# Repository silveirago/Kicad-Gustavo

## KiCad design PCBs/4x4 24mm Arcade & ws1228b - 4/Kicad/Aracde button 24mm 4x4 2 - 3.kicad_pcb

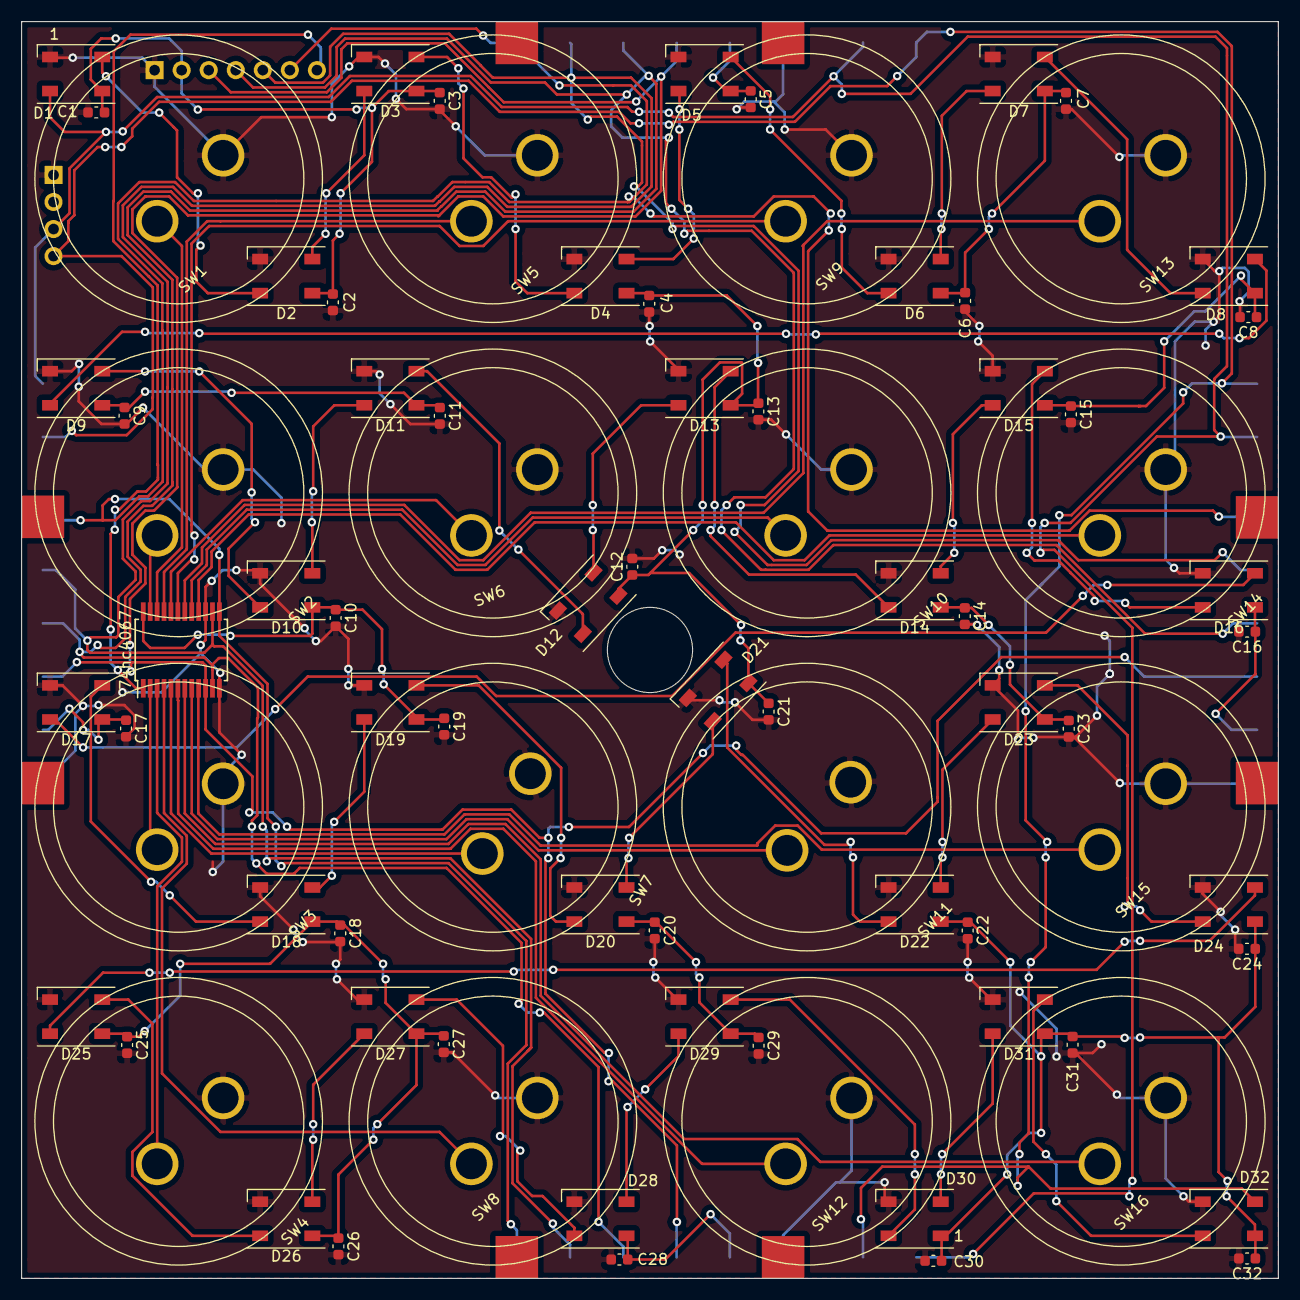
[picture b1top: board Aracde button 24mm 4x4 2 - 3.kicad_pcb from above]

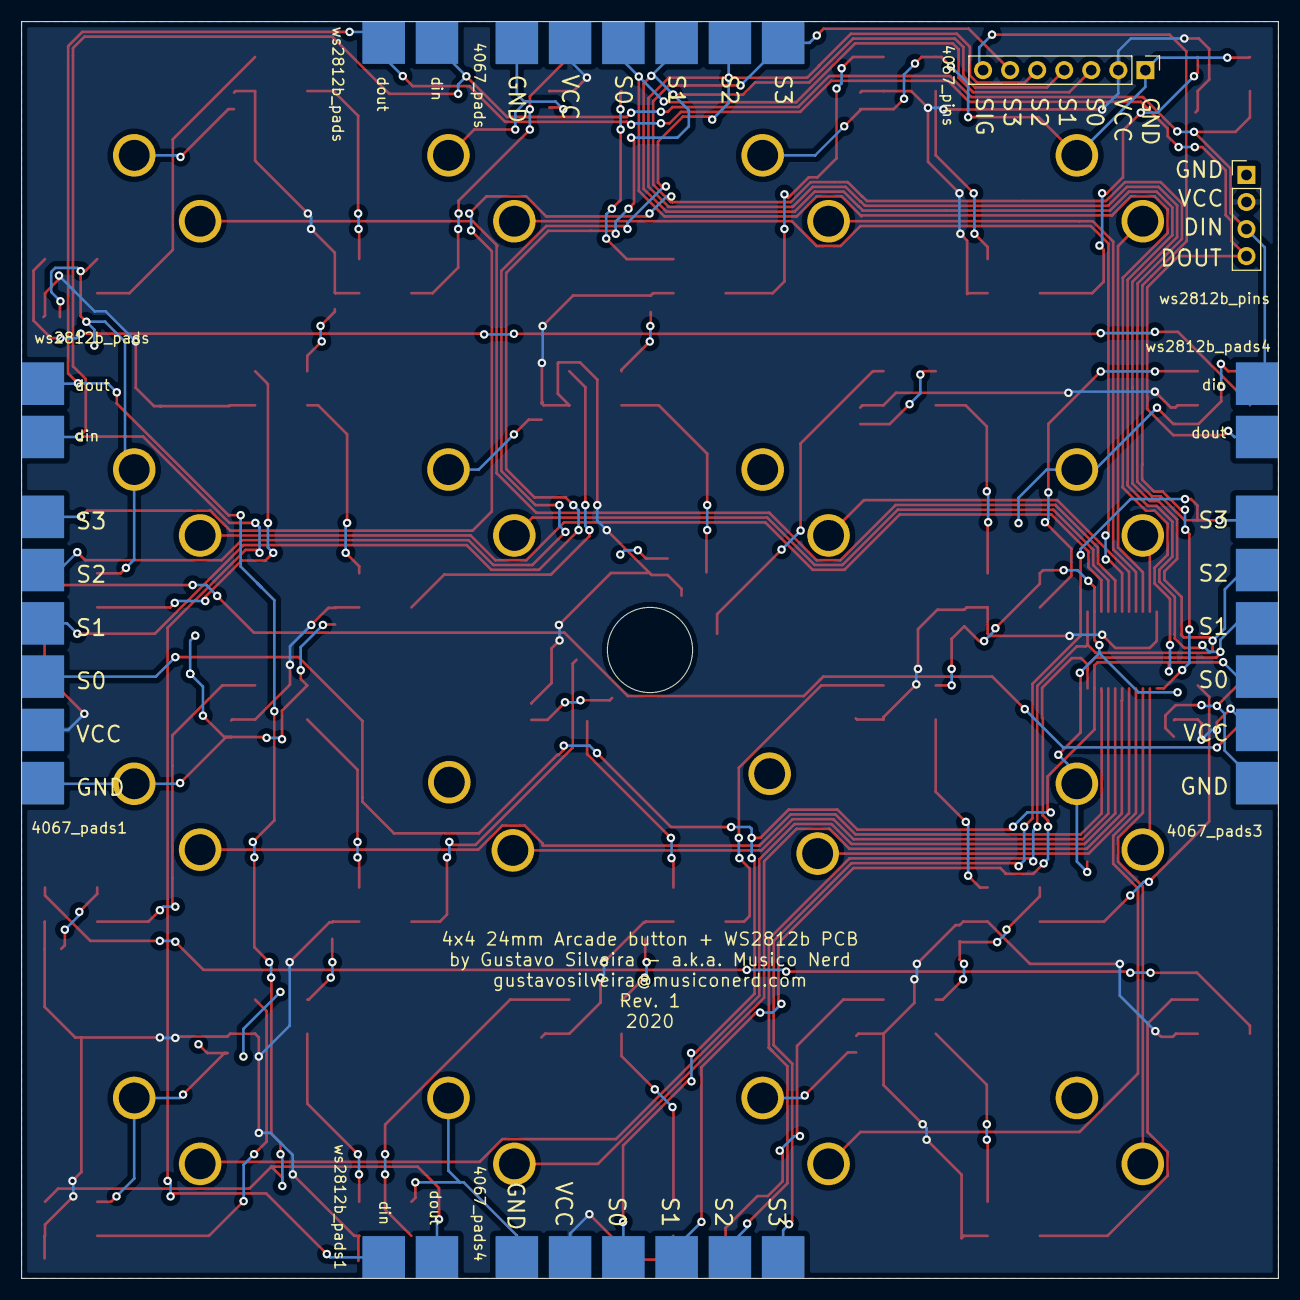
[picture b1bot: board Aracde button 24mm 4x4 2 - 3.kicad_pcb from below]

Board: 2 copper layers, 118.0 x 118.0 mm, 91 parts (10 on the bottom side), 56 nets.

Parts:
74hc4067: CD74HC4067M; SSOP-24_5.3x8.2mm_P0.65mm
4067_pads, 4067_pads1, 4067_pads3, 4067_pads4: Conn_01x06_Female; pad_connector_small_6
4067_pins: Conn_01x07_Female; PinHeader_1x07_P2.54mm_Vertical
C1, C2, C3, C4, C5, C6, C7, C8, C9, C10, C11, C12, C13, C14, C15, C16, C17, C18, C19, C20, C21, C22, C23, C24, C25, C26, C27, C28, C29, C30, C31, C32: 100nF; C_0603_1608Metric
D1, D2, D3, D4, D5, D6, D7, D8, D9, D10, D11, D12, D13, D14, D15, D16, D17, D18, D19, D20, D21, D22, D23, D24, D25, D26, D27, D28, D29, D30, D31, D32: WS2812B; LED_WS2812B_PLCC4_5.0x5.0mm_P3.2mm
SW1, SW2, SW3, SW4, SW5, SW6, SW7, SW8, SW9, SW10, SW11, SW12, SW13, SW14, SW15, SW16: SW_SPST; Arcade button 24mm
ws2812b_pads, ws2812b_pads1, ws2812b_pads4, ws2812b_pads#2: Conn_01x02_Female; pad_connector_small_2
ws2812b_pins: Conn_01x04_Female; PinHeader_1x04_P2.54mm_Vertical

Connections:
/S0: 74hc4067.10, 4067_pads.3, 4067_pads1.3, 4067_pads3.3, 4067_pads4.3, 4067_pins.3
/S1: 74hc4067.11, 4067_pads.4, 4067_pads1.4, 4067_pads3.4, 4067_pads4.4, 4067_pins.4
/S2: 74hc4067.14, 4067_pads.5, 4067_pads1.5, 4067_pads3.5, 4067_pads4.5, 4067_pins.5
/S3: 74hc4067.13, 4067_pads.6, 4067_pads1.6, 4067_pads3.6, 4067_pads4.6, 4067_pins.6
/SIG: 74hc4067.1, 4067_pins.7
/din: D1.4, ws2812b_pads.1, ws2812b_pads1.1, ws2812b_pads4.2, ws2812b_pads#2.2, ws2812b_pins.3
/dout: D32.2, ws2812b_pads.2, ws2812b_pads1.2, ws2812b_pads4.1, ws2812b_pads#2.1, ws2812b_pins.4
/mux_0: 74hc4067.9, SW15.1
/mux_1: 74hc4067.8, SW11.1
/mux_2: 74hc4067.7, SW16.1
/mux_3: 74hc4067.6, SW12.1
/mux_4: 74hc4067.5, SW7.1
/mux_5: 74hc4067.4, SW8.1
/mux_6: 74hc4067.3, SW4.1
/mux_7: 74hc4067.2, SW3.1
/mux_8: 74hc4067.23, SW2.1
/mux_9: 74hc4067.22, SW1.1
/mux_10: 74hc4067.21, SW5.1
/mux_11: 74hc4067.20, SW6.1
/mux_12: 74hc4067.19, SW9.1
/mux_13: 74hc4067.18, SW13.1
/mux_14: 74hc4067.17, SW10.1
/mux_15: 74hc4067.16, SW14.1
GND: 74hc4067.12, 74hc4067.15, 4067_pads.1, 4067_pads1.1, 4067_pads3.1, 4067_pads4.1, 4067_pins.1, C1.2, C2.2, C3.2, C4.2, C5.2, C6.2, C7.2, C8.2, C9.2, C10.2, C11.2, C12.2, C13.2, C14.2, C15.2, C16.2, C17.2, C18.2, C19.2, C20.2, C21.2, C22.2, C23.2, C24.2, C25.2, C26.2, C27.2, C28.2, C29.2, C30.2, C31.2, C32.2, D1.3, D2.3, D3.3, D4.3, D5.3, D6.3, D7.3, D8.3, D9.3, D10.3, D11.3, D12.3, D13.3, D14.3, D15.3, D16.3, D17.3, D18.3, D19.3, D20.3, D21.3, D22.3, D23.3, D24.3, D25.3, D26.3, D27.3, D28.3, D29.3, D30.3, D31.3, D32.3, SW1.2, SW2.2, SW3.2, SW4.2, SW5.2, SW6.2, SW7.2, SW8.2, SW9.2, SW10.2, SW11.2, SW12.2, SW13.2, SW14.2, SW15.2, SW16.2, ws2812b_pins.1
unnamed: D1.2, D2.4
unnamed: D2.2, D3.4
unnamed: D3.2, D4.4
unnamed: D4.2, D5.4
unnamed: D5.2, D6.4
unnamed: D6.2, D7.4
unnamed: D7.2, D8.4
unnamed: D8.2, D9.4
unnamed: D10.2, D11.4
unnamed: D9.2, D10.4
unnamed: D11.2, D12.4
unnamed: D12.2, D13.4
unnamed: D13.2, D14.4
unnamed: D14.2, D15.4
unnamed: D15.2, D16.4
unnamed: D16.2, D17.4
unnamed: D17.2, D18.4
unnamed: D18.2, D19.4
unnamed: D19.2, D20.4
unnamed: D20.2, D21.4
unnamed: D21.2, D22.4
unnamed: D22.2, D23.4
unnamed: D23.2, D24.4
unnamed: D24.2, D25.4
unnamed: D25.2, D26.4
unnamed: D26.2, D27.4
unnamed: D27.2, D28.4
unnamed: D28.2, D29.4
unnamed: D29.2, D30.4
unnamed: D30.2, D31.4
unnamed: D31.2, D32.4
VCC: 74hc4067.24, 4067_pads.2, 4067_pads1.2, 4067_pads3.2, 4067_pads4.2, 4067_pins.2, C1.1, C2.1, C3.1, C4.1, C5.1, C6.1, C7.1, C8.1, C9.1, C10.1, C11.1, C12.1, C13.1, C14.1, C15.1, C16.1, C17.1, C18.1, C19.1, C20.1, C21.1, C22.1, C23.1, C24.1, C25.1, C26.1, C27.1, C28.1, C29.1, C30.1, C31.1, C32.1, D1.1, D2.1, D3.1, D4.1, D5.1, D6.1, D7.1, D8.1, D9.1, D10.1, D11.1, D12.1, D13.1, D14.1, D15.1, D16.1, D17.1, D18.1, D19.1, D20.1, D21.1, D22.1, D23.1, D24.1, D25.1, D26.1, D27.1, D28.1, D29.1, D30.1, D31.1, D32.1, ws2812b_pins.2

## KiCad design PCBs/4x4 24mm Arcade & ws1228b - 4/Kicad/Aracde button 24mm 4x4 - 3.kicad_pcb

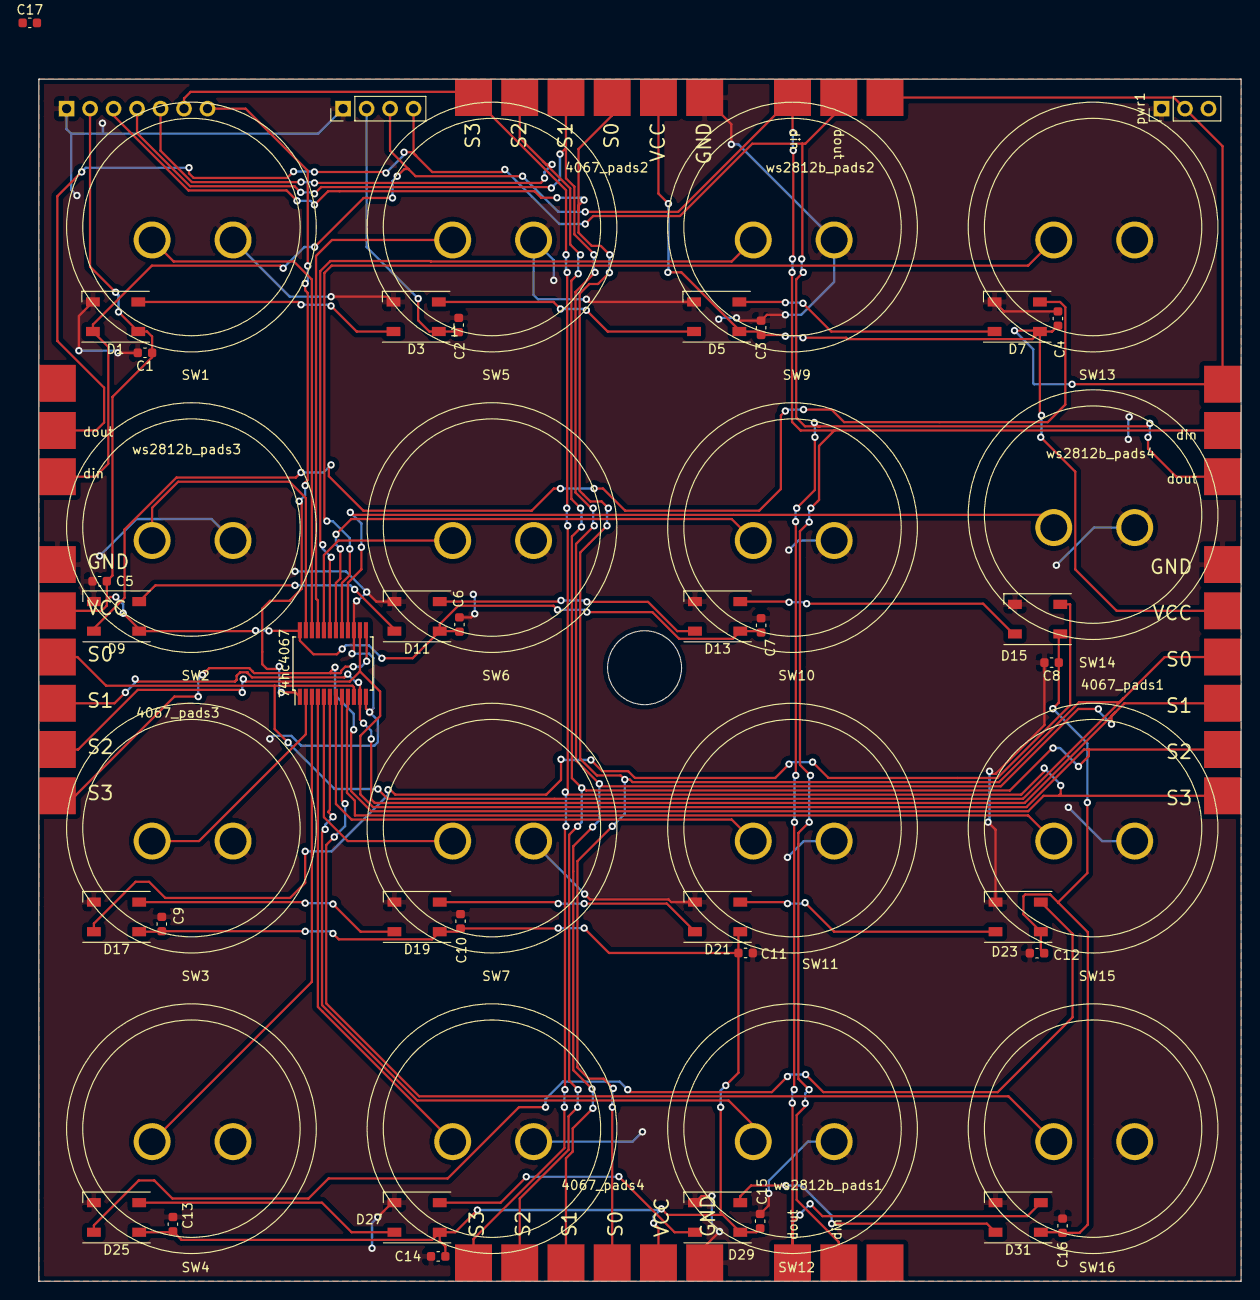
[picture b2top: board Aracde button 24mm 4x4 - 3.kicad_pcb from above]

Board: 2 copper layers, 130.0 x 130.0 mm, 65 parts (1 on the bottom side), 41 nets.

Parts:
5v1, 5v2, 5v3, 5v4: pad_5v; Pad_connector_small
74hc4067: CD74HC4067M; SSOP-24_5.3x8.2mm_P0.65mm
4067_pads1, 4067_pads2, 4067_pads3, 4067_pads4: Conn_01x06_Female; pad_connector_small_6
4067_pins1: Conn_01x07_Female; PinHeader_1x07_P2.54mm_Vertical
C1, C2, C3, C4, C5, C6, C7, C8, C9, C10, C11, C12, C13, C14, C15, C16, C17: 100nF; C_0603_1608Metric
D1, D3, D5, D7, D9, D11, D13, D15, D17, D19, D21, D23, D25, D27, D29, D31: WS2812B; LED_WS2812B_PLCC4_5.0x5.0mm_P3.2mm
SW1, SW2, SW3, SW4, SW5, SW6, SW7, SW8, SW9, SW10, SW11, SW12, SW13, SW14, SW15, SW16: SW_SPST; Arcade button 24mm
pwr1: Conn_01x03_Female; PinHeader_1x03_P2.54mm_Vertical
ws2812b_pads1, ws2812b_pads2, ws2812b_pads3, ws2812b_pads4: Conn_01x02_Female; pad_connector_small_2
ws2812b_pins4: Conn_01x04_Female; PinHeader_1x04_P2.54mm_Vertical

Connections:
+5V: 5v1.1, 5v2.1, 5v3.1, 5v4.1, C1.1, C2.1, C3.1, C4.1, C5.1, C6.1, C7.1, C8.1, C9.1, C10.1, C11.1, C12.1, C13.1, C14.1, C15.1, C16.1, D1.1, D3.1, D5.1, D7.1, D9.1, D11.1, D13.1, D15.1, D17.1, D19.1, D21.1, D23.1, D25.1, D27.1, D29.1, D31.1, pwr1.2, ws2812b_pins4.2
/S0: 74hc4067.10, 4067_pads1.3, 4067_pads2.3, 4067_pads3.3, 4067_pads4.3, 4067_pins1.3
/S1: 74hc4067.11, 4067_pads1.4, 4067_pads2.4, 4067_pads3.4, 4067_pads4.4, 4067_pins1.4
/S2: 74hc4067.14, 4067_pads1.5, 4067_pads2.5, 4067_pads3.5, 4067_pads4.5, 4067_pins1.5
/S3: 74hc4067.13, 4067_pads1.6, 4067_pads2.6, 4067_pads3.6, 4067_pads4.6, 4067_pins1.6
/SIG: 74hc4067.1, 4067_pins1.7
/din: D1.4, ws2812b_pads1.1, ws2812b_pads2.2, ws2812b_pads3.1, ws2812b_pads4.2, ws2812b_pins4.3
/dout: D31.2, ws2812b_pads1.2, ws2812b_pads2.1, ws2812b_pads3.2, ws2812b_pads4.1, ws2812b_pins4.4
/mux_0: 74hc4067.9, SW15.1
/mux_1: 74hc4067.8, SW16.1
/mux_2: 74hc4067.7, SW11.1
/mux_3: 74hc4067.6, SW12.1
/mux_4: 74hc4067.5, SW7.1
/mux_5: 74hc4067.4, SW8.1
/mux_6: 74hc4067.3, SW4.1
/mux_7: 74hc4067.2, SW3.1
/mux_8: 74hc4067.23, SW2.1
/mux_9: 74hc4067.22, SW1.1
/mux_10: 74hc4067.21, SW5.1
/mux_11: 74hc4067.20, SW6.1
/mux_12: 74hc4067.19, SW9.1
/mux_13: 74hc4067.18, SW10.1
/mux_14: 74hc4067.17, SW13.1
/mux_15: 74hc4067.16, SW14.1
GND: 74hc4067.12, 74hc4067.15, 4067_pads1.1, 4067_pads2.1, 4067_pads3.1, 4067_pads4.1, 4067_pins1.1, C1.2, C2.2, C3.2, C4.2, C5.2, C6.2, C7.2, C8.2, C9.2, C10.2, C11.2, C12.2, C13.2, C14.2, C15.2, C16.2, C17.1, D1.3, D3.3, D5.3, D7.3, D9.3, D11.3, D13.3, D15.3, D17.3, D19.3, D21.3, D23.3, D25.3, D27.3, D29.3, D31.3, SW1.2, SW2.2, SW3.2, SW4.2, SW5.2, SW6.2, SW7.2, SW8.2, SW9.2, SW10.2, SW11.2, SW12.2, SW13.2, SW14.2, SW15.2, SW16.2, pwr1.1, ws2812b_pins4.1
unnamed: D1.2, D3.4
unnamed: D3.2, D5.4
unnamed: D5.2, D7.4
unnamed: D7.2, D9.4
unnamed: D11.2, D13.4
unnamed: D9.2, D11.4
unnamed: D13.2, D15.4
unnamed: D15.2, D17.4
unnamed: D17.2, D19.4
unnamed: D19.2, D21.4
unnamed: D21.2, D23.4
unnamed: D23.2, D25.4
unnamed: D25.2, D27.4
unnamed: D27.2, D29.4
unnamed: D29.2, D31.4
VCC: 74hc4067.24, 4067_pads1.2, 4067_pads2.2, 4067_pads3.2, 4067_pads4.2, 4067_pins1.2, C17.2, pwr1.3

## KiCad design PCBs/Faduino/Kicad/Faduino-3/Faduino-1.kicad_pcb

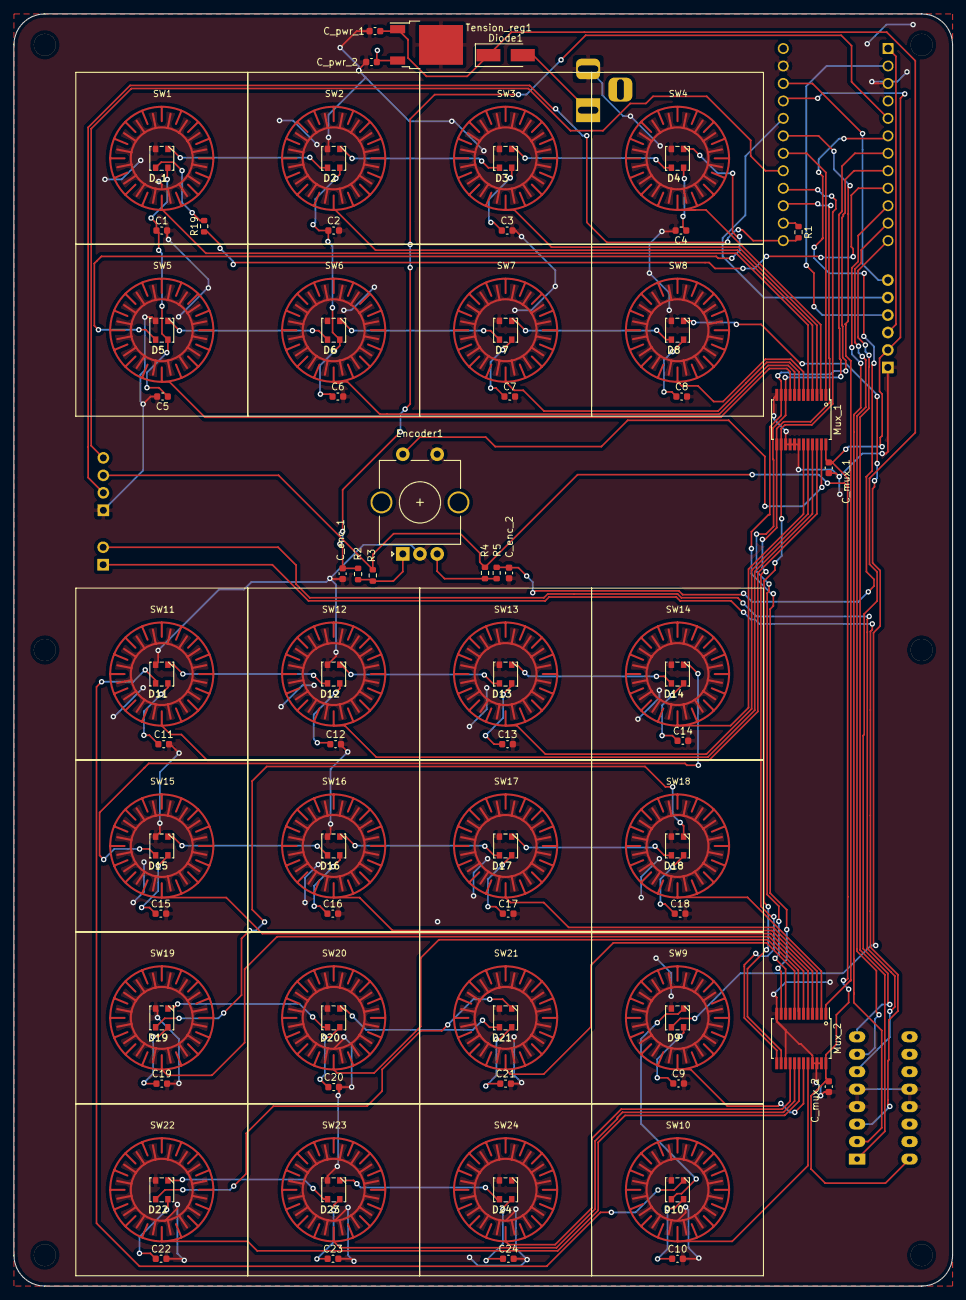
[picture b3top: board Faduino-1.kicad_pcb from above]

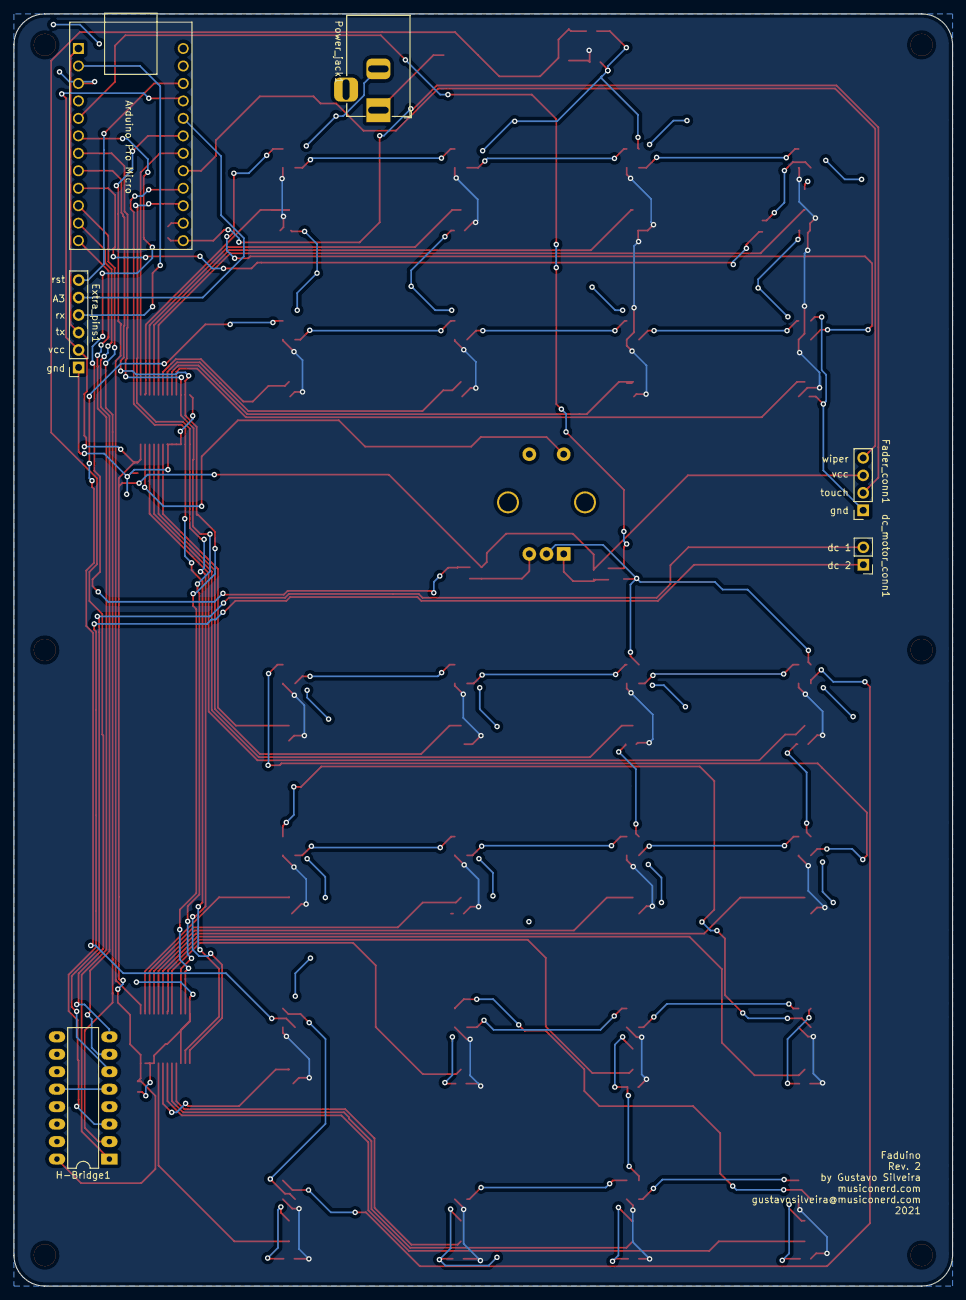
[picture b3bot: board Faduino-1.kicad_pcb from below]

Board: 2 copper layers, 136.5 x 185.0 mm, 95 parts (6 on the bottom side), 77 nets.

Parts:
Arduino Pro Micro: Arduino_Pro_Micro; ArduinoProMicro
C1, C2, C3, C4, C5, C6, C7, C8, C9, C10, C11, C12, C13, C14, C15, C16, C17, C18, C19, C20, C21, C22, C23, C24: 100nF; C_0603_1608Metric
C_enc_1, C_enc_2: 10nF; C_0603_1608Metric
C_mux_1, C_mux_2: 100nF; C_0603_1608Metric
C_pwr_1: 330nF; C_0603_1608Metric
C_pwr_2: 100nF; C_0603_1608Metric
D2, D3, D4, D5, D6, D7, D8, D9, D10, D11, D12, D13, D14, D15, D16, D17, D18, D19, D20, D21, D22, D23, D24: WS2812B; WS2812B-mini-V3
D_1: WS2812B; WS2812B-mini-V3
Diode1: 1N4007; D_SMA_Handsoldering
Encoder1: Rotary_Encoder_Switch; RotaryEncoder_Alps_EC11E-Switch_Vertical_H20mm_CircularMoun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
Extra_pins1: Conn_01x06; PinSocket_1x06_P2.54mm_Vertical
Fader_conn1: Conn_01x04; PinSocket_1x04_P2.54mm_Vertical
H-Bridge1: L293D; DIP-16_W7.62mm_LongPads
Mux_1, Mux_2: CD74HC4067M_2; SSOP-24_5.3x8.2mm_P0.65mm
Power_jack1: Jack-DC; BarrelJack_Horizontal
R1: 1M; R_0603_1608Metric
R2, R3, R4, R5: 10k; R_0603_1608Metric
R19: 330; R_0603_1608Metric
SW1, SW2, SW3, SW4, SW5, SW6, SW7, SW8, SW9, SW10, SW11, SW12, SW13, SW14, SW15, SW16, SW17, SW18, SW19, SW20, SW21, SW22, SW23, SW24: SW_SPST; rubber_pad_sw_5
Tension_reg1: L7805; TO-252-2
dc_motor_conn1: Conn_01x02; PinHeader_1x02_P2.54mm_Vertical

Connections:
5V: C1.1, C2.1, C3.1, C4.1, C5.1, C6.1, C7.1, C8.1, C9.1, C10.1, C11.1, C12.1, C13.1, C14.1, C15.1, C16.1, C17.1, C18.1, C19.1, C20.1, C21.1, C22.1, C23.1, C24.1, C_pwr_2.1, D2.1, D3.1, D4.1, D5.1, D6.1, D7.1, D8.1, D9.1, D10.1, D11.1, D12.1, D13.1, D14.1, D15.1, D16.1, D17.1, D18.1, D19.1, D20.1, D21.1, D22.1, D23.1, D24.1, D_1.1, Tension_reg1.3
9V: C_pwr_1.1, Diode1.1, H-Bridge1.8, Tension_reg1.1
/A3: Arduino Pro Micro.20, Extra_pins1.5
/RST: Arduino Pro Micro.22, Extra_pins1.6
/RX: Arduino Pro Micro.2, Extra_pins1.4
/TX: Arduino Pro Micro.1, Extra_pins1.3
ENC_A: Arduino Pro Micro.5, C_enc_1.1, R2.2
ENC_B: Arduino Pro Micro.6, C_enc_2.1, R5.1
ENC_SW: Encoder1.S2, Mux_1.23
F_ENABLE: Arduino Pro Micro.12, H-Bridge1.1
F_IN_1: Arduino Pro Micro.10, H-Bridge1.2
F_IN_2: Arduino Pro Micro.11, H-Bridge1.7
F_OUT_1: H-Bridge1.3, dc_motor_conn1.1
F_OUT_2: H-Bridge1.6, dc_motor_conn1.2
F_TOUCH_1: Arduino Pro Micro.13, Fader_conn1.2, R1.2
F_TOUCH_2: Arduino Pro Micro.14, R1.1
F_WIPER: Arduino Pro Micro.17, Fader_conn1.4
GND: Arduino Pro Micro.3, Arduino Pro Micro.4, Arduino Pro Micro.23, C1.2, C2.2, C3.2, C4.2, C5.2, C6.2, C7.2, C8.2, C9.2, C10.2, C11.2, C12.2, C13.2, C14.2, C15.2, C16.2, C17.2, C18.2, C19.2, C20.2, C21.2, C22.2, C23.2, C24.2, C_enc_1.2, C_enc_2.2, C_mux_1.2, C_mux_2.2, C_pwr_1.2, C_pwr_2.2, D2.3, D3.3, D4.3, D5.3, D6.3, D7.3, D8.3, D9.3, D10.3, D11.3, D12.3, D13.3, D14.3, D15.3, D16.3, D17.3, D18.3, D19.3, D20.3, D21.3, D22.3, D23.3, D24.3, D_1.3, Encoder1.C, Encoder1.S1, Extra_pins1.1, Fader_conn1.1, H-Bridge1.4, H-Bridge1.5, H-Bridge1.12, H-Bridge1.13, Mux_1.12, Mux_1.15, Mux_1.16, Mux_1.17, Mux_1.18, Mux_2.12, Mux_2.15, Mux_2.21, Mux_2.22, Mux_2.23, Power_jack1.2, SW1.1, SW2.1, SW3.1, SW4.1, SW5.1, SW6.1, SW7.1, SW8.1, SW9.1, SW10.1, SW11.1, SW12.1, SW13.1, SW14.1, SW15.1, SW16.1, SW17.1, SW18.1, SW19.1, SW20.1, SW21.1, SW22.1, SW23.1, SW24.1, Tension_reg1.2
unnamed: D2.2, D3.4
unnamed: D2.4, D_1.2
unnamed: D3.2, D4.4
unnamed: D4.2, D5.4
unnamed: D5.2, D6.4
unnamed: D6.2, D7.4
unnamed: D7.2, D8.4
unnamed: D8.2, D9.4
unnamed: D10.2, D11.4
unnamed: D9.2, D10.4
unnamed: D11.2, D12.4
unnamed: D12.2, D13.4
unnamed: D13.2, D14.4
unnamed: D14.2, D15.4
unnamed: D15.2, D16.4
unnamed: D16.2, D17.4
unnamed: D17.2, D18.4
unnamed: D18.2, D19.4
unnamed: D19.2, D20.4
unnamed: D20.2, D21.4
unnamed: D21.2, D22.4
unnamed: D22.2, D23.4
unnamed: D23.2, D24.4
unnamed: D_1.4, R19.2
unnamed: Diode1.2, Power_jack1.1
unnamed: Encoder1.A, R2.1, R3.1
unnamed: Encoder1.B, R4.1, R5.2
unnamed: Mux_1.2, SW4.2
unnamed: Mux_1.3, SW3.2
unnamed: Mux_1.4, SW2.2
unnamed: Mux_1.5, SW1.2
unnamed: Mux_1.6, SW8.2
unnamed: Mux_1.7, SW7.2
unnamed: Mux_1.8, SW6.2
unnamed: Mux_1.9, SW5.2
unnamed: Mux_1.19, SW14.2
unnamed: Mux_1.20, SW13.2
unnamed: Mux_1.21, SW12.2
unnamed: Mux_1.22, SW11.2
unnamed: Mux_2.2, SW18.2
unnamed: Mux_2.3, SW17.2
unnamed: Mux_2.4, SW16.2
unnamed: Mux_2.5, SW15.2
unnamed: Mux_2.6, SW19.2
unnamed: Mux_2.7, SW20.2
unnamed: Mux_2.8, SW21.2
unnamed: Mux_2.16, SW24.2
unnamed: Mux_2.17, SW23.2
unnamed: Mux_2.18, SW22.2
unnamed: Mux_2.19, SW9.2
unnamed: Mux_2.20, SW10.2
S0: Arduino Pro Micro.7, Mux_1.10, Mux_2.10
S1: Arduino Pro Micro.8, Mux_1.11, Mux_2.11
S2: Arduino Pro Micro.16, Mux_1.14, Mux_2.14
S3: Arduino Pro Micro.15, Mux_1.13, Mux_2.13
SIG_1: Arduino Pro Micro.18, Mux_1.1
SIG_2: Arduino Pro Micro.19, Mux_2.1
VCC: Arduino Pro Micro.21, C_mux_1.1, C_mux_2.1, Extra_pins1.2, Fader_conn1.3, H-Bridge1.16, Mux_1.24, Mux_2.24, R3.2, R4.2
addressable_led: Arduino Pro Micro.9, R19.1

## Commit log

2017-07-28 libs added
2017-07-28 teste
2017-07-29 adds
2022-02-05 teensy added
2022-02-05 rubber pad, arduino shields
2022-02-11 4067 and display added
2022-02-17 deleted folder
2022-02-17 folder fixed
2022-07-29 rubber pad
2022-07-29 files added
